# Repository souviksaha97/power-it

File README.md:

# power-it

100 W Electronic DC Load developed during the course of my Final Year Project.
Changes made will be updated.

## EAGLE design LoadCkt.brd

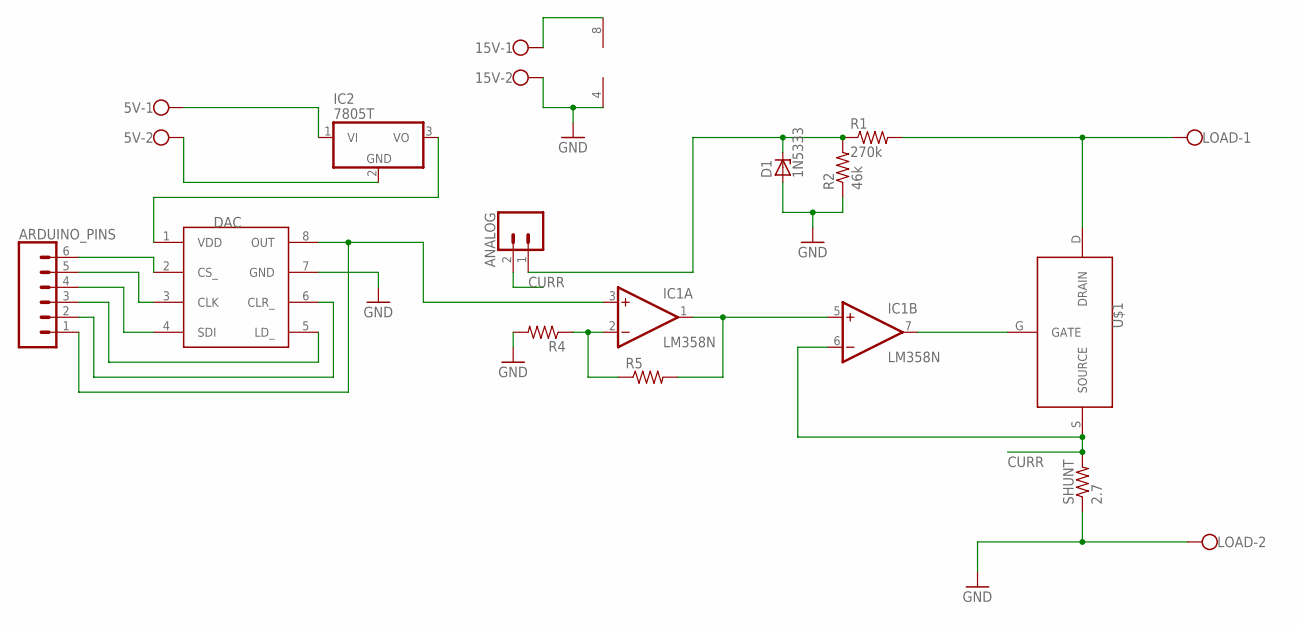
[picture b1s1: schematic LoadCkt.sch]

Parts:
5V, 15V: W237-102
ANALOG: CONN_02; 1X02
ARDUINO_PINS: CONN_06SILK_FEMALE_PTH; 1X06
D1: 1N5333; C1702-15
DAC: DAC7611DIP; DP-04
IC1: LM358N; DIL08
IC2: 7805T; TO220H
LOAD: W237-102
R1: 270k; 0204/7
R2: 46k; 0204/7
R4, R5: R-US_0204/7; 0204/7
SHUNT: 2.7; 0204/7
U$1: IRFP4468; TO-247AD-H

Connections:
CURR: ANALOG.2, IC1.6 (-IN), SHUNT.2, U$1.S (SOURCE)
GND: 15V.2, D1.A, DAC.7 (GND), IC1.4 (V-), LOAD.2, R2.1, R4.2, SHUNT.1
unnamed: ANALOG.1, D1.C, R1.1, R2.2
unnamed: 5V.1, IC2.1 (VI)
unnamed: 5V.2, IC2.2 (GND)
unnamed: DAC.1 (VDD), IC2.3 (VO)
unnamed: ARDUINO_PINS.6, DAC.2 (CS_)
unnamed: ARDUINO_PINS.5, DAC.3 (CLK)
unnamed: ARDUINO_PINS.4, DAC.4 (SDI)
unnamed: ARDUINO_PINS.3, DAC.5 (LD_)
unnamed: ARDUINO_PINS.2, DAC.6 (CLR_)
unnamed: ARDUINO_PINS.1, DAC.8 (OUT), IC1.3 (+IN)
unnamed: LOAD.1, R1.2, U$1.D (DRAIN)
unnamed: IC1.7 (OUT), U$1.G (GATE)
unnamed: IC1.2 (-IN), R4.1, R5.1
unnamed: IC1.1 (OUT), IC1.5 (+IN), R5.2
unnamed: 15V.1, IC1.8 (V+)

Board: 2 copper layers, 15 parts (0 on the bottom side), 17 nets, no tracks yet.

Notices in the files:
parts and their libraries:
SparkFun-Connectors: Licensing: Creative Commons ShareAlike 4.0 International - https://creativecommons.org/licenses/by-sa/4.0
